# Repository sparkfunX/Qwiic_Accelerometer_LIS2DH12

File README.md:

Qwiic Accelerometer LIS2DH12
=======================================

This MEMS, three axis accelerometer by STMicroelectronics has been outfitted to communicate over Qwiic. The LIS2DH12 is an ultra-low-power highperformance three-axis linear accelerometer belonging to the “femto” family with digital I2C/SPI serial interface standard output.

Repository Contents
-------------------

* **/Hardware** - Eagle design files (.brd, .sch)
* **/Documents** - Documentation
* **/LIS2DH12_test** - Test Script

License Information
-------------------

This product is _**open source**_! 

Please review the LICENSE.md file for license information. 

If you have any questions or concerns on licensing, please contact technical support on our [SparkFun forums](https://forum.sparkfun.com/viewforum.php?f=152).

Distributed as-is; no warranty is given.

- Your friends at SparkFun.

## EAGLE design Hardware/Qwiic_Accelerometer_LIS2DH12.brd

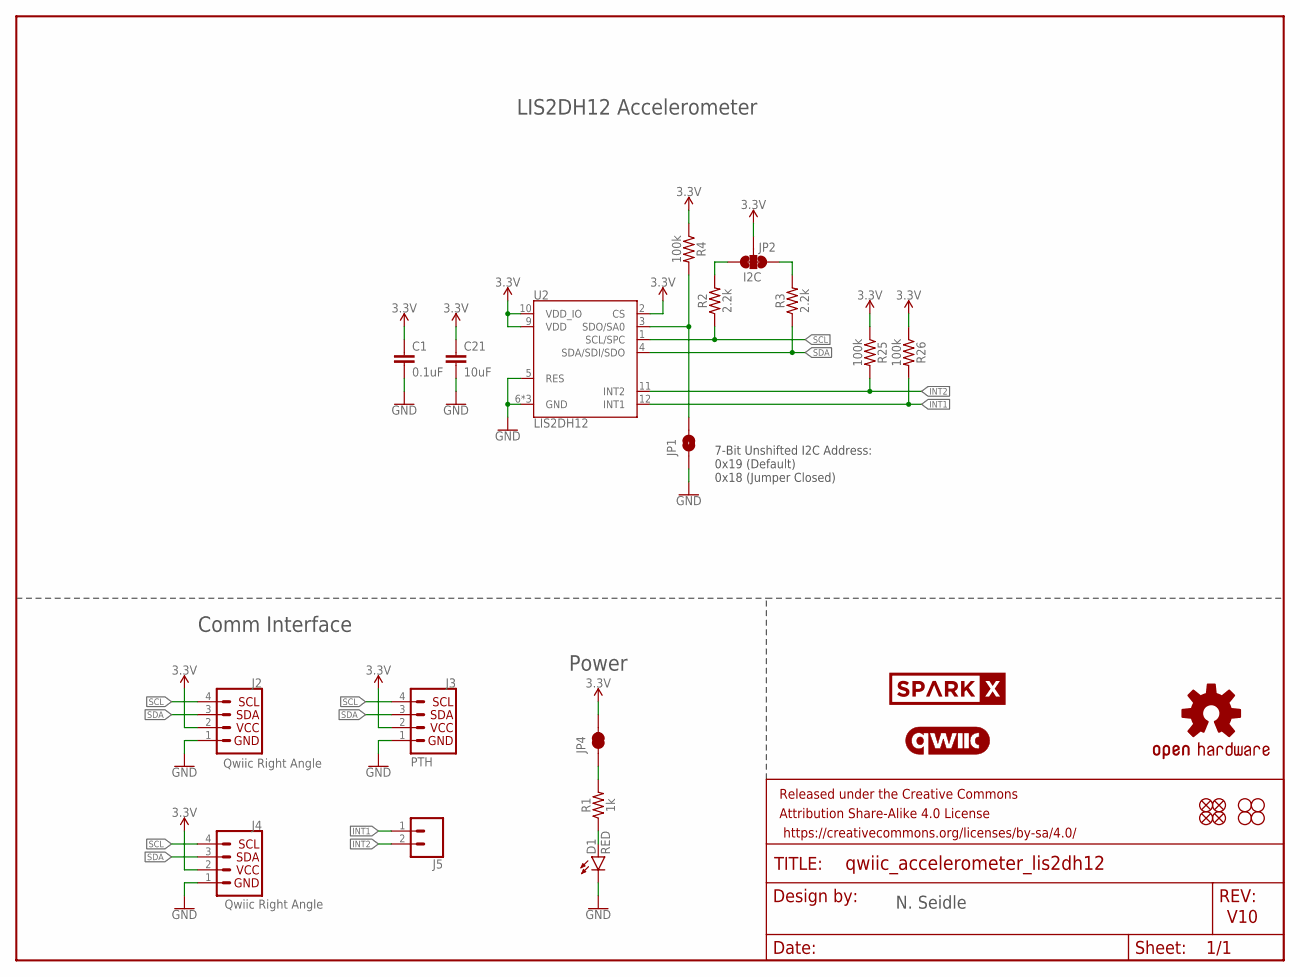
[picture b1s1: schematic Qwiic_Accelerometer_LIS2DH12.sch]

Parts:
C1: 0.1uF; 0603
C21: 10uF; 0603
D1: RED; LED-0603
FD1, FD2, FD3, FD4: FIDUCIALUFIDUCIAL; FIDUCIAL-MICRO
FRAME1: FRAME-LETTER; CREATIVE_COMMONS
H1, H2, H3, H4: STAND-OFF
J2, J4: Qwiic Right Angle; JST04_1MM_RA
J3: PTH; 1X04_NO_SILK
J5: CONN_021X02_NO_SILK; 1X02_NO_SILK
JP1: JUMPER-SMT_2_NO_SILK; SMT-JUMPER_2_NO_SILK
JP2: I2C; SMT-JUMPER_3_2-NC_TRACE_SILK
JP4: JUMPER-SMT_2_NC_TRACE_SILK; SMT-JUMPER_2_NC_TRACE_SILK
LOGO1: OSHW-LOGOMINI; OSHW-LOGO-MINI
LOGO4: QWIIC_LOGO_CONNECTOR; QWIIC_5.5MM
R1: 1k; 0603
R2, R3: 2.2k; 0603
R4, R25, R26: 100k; 0603
U2: LIS2DH12; LGA-12-LISDH12
U$30: SPARKX-LOGO4; SPARKX-MEDIUM

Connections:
3.3V: C1.1, C21.1, J2.2, J3.2, J4.2, JP2.2, JP4.2, R4.1, R25.1, R26.1, U2.2 (CS), U2.9 (VDD), U2.10 (VDD_IO)
GND: C1.2, C21.2, D1.C, J2.1, J3.1, J4.1, JP1.1, U2.5 (RES), U2.6 (GND), U2.7 (GND), U2.8 (GND)
INT1: J5.1, R26.2, U2.12 (INT1)
INT2: J5.2, R25.2, U2.11 (INT2)
unnamed: JP4.1, R1.2
unnamed: JP2.1, R3.2
unnamed: JP2.3, R2.2
unnamed: JP1.2, R4.2, U2.3 (SDO/SA0)
unnamed: D1.A, R1.1
SCL: J2.4, J3.4, J4.4, R2.1, U2.1 (SCL/SPC)
SDA: J2.3, J3.3, J4.3, R3.1, U2.4 (SDA/SDI/SDO)

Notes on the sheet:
V10
N. Seidle
LIS2DH12 Accelerometer
Comm Interface
Power
7-Bit Unshifted I2C Address: 0x19 (Default) 0x18 (Jumper Closed)

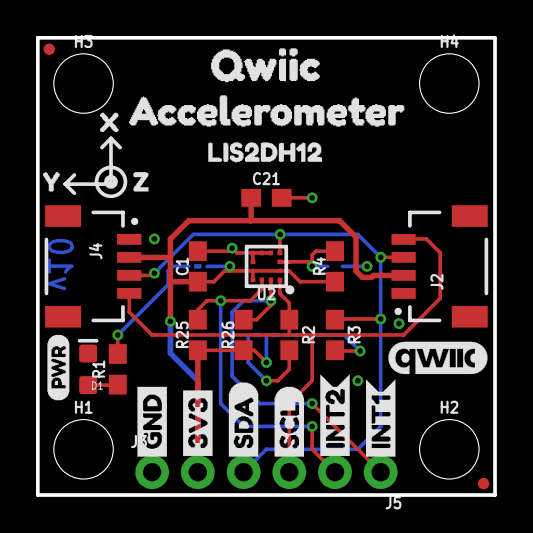
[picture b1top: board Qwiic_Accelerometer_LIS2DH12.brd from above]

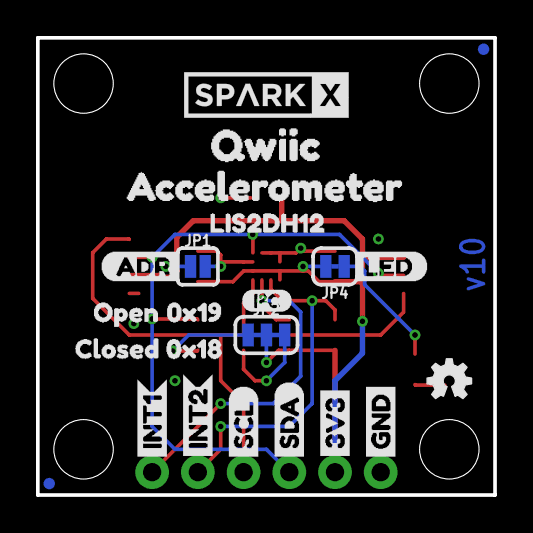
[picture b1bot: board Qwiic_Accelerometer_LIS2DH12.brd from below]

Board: 2 copper layers, 25.4 x 25.4 mm, 58 parts (23 on the bottom side), 11 nets.

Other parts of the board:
U$1, U$4: SDA-[)
U$2: X0
U$3, U$5: SCL-[)
U$6, U$7: 3V3-04
U$8, U$9: GND-04
U$10, U$27: ACCELEROMETER2
U$11, U$12: INT13
U$13, U$15: INT24
U$14, U$22: QWIIC2
U$16: 0X183
U$17, U$28: LIS2DH120
U$18: PWR-()-03
U$19: I_SUPER2_C-()-03
U$20: Y1
U$21: Z2
U$23: 0X192
U$24: ADR1
U$25: CLOSED4
U$26: OPEN5
U$29: LED7

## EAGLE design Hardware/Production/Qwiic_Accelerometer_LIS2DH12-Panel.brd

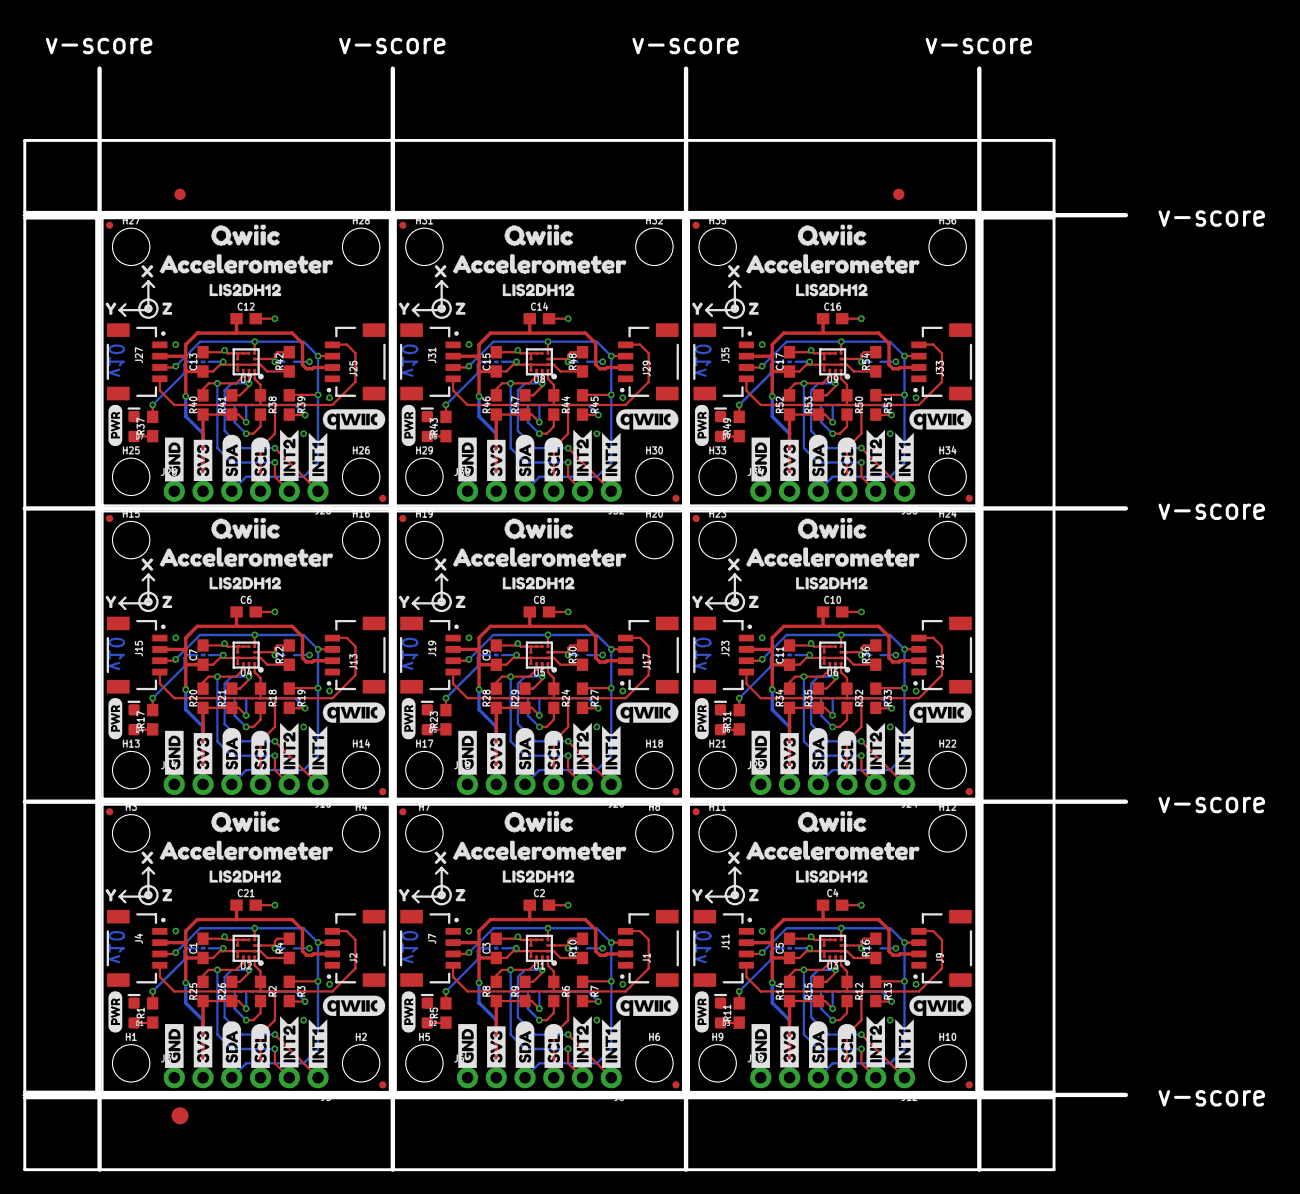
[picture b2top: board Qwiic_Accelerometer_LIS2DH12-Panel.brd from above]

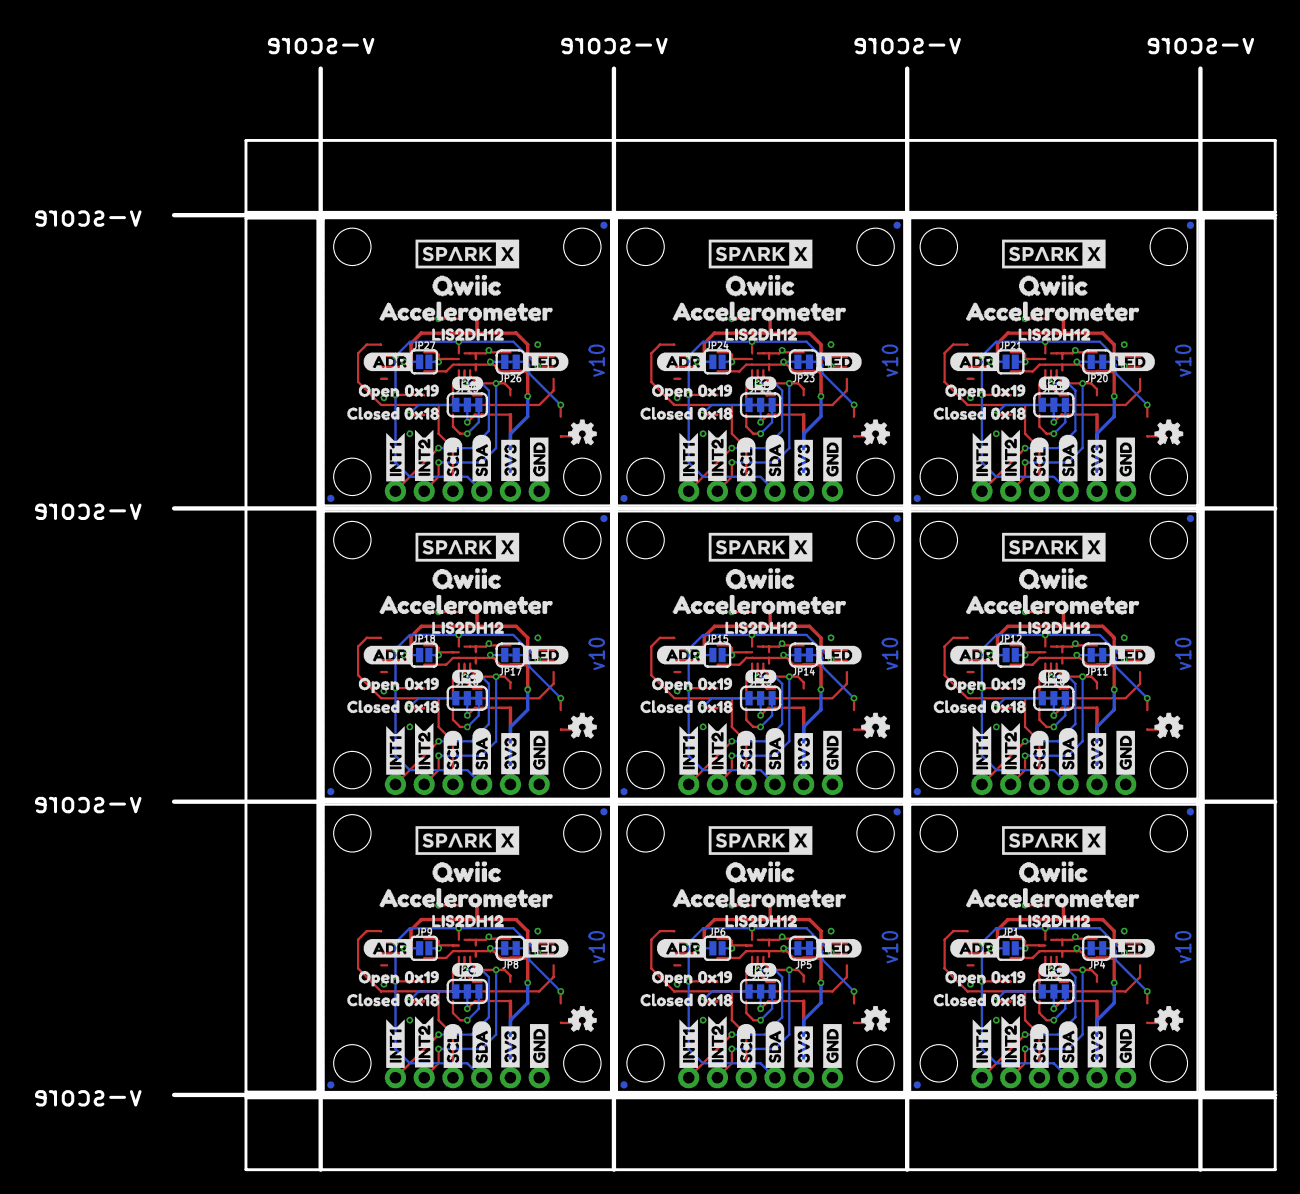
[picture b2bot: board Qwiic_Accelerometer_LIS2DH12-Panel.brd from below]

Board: 2 copper layers, 110.5 x 101.2 mm, 516 parts (207 on the bottom side), 99 nets.

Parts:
C1, C3, C5, C7, C9, C11, C13, C15, C17: 0.1uF; 0603
C2, C4, C6, C8, C10, C12, C14, C16, C21: 10uF; 0603
D1, D2, D3, D4, D5, D6, D7, D8, D9: RED; LED-0603
E$1, E$2: FIDUCIAL-1X2
E$3: FIDUCIAL-1.5X3
FD1, FD2, FD3, FD4, FD5, FD6, FD7, FD8, FD9, FD10, FD11, FD12, FD13, FD14, FD15, FD16, FD17, FD18, FD19, FD20, FD21, FD22, FD23, FD24, FD25, FD26, FD27, FD28, FD29, FD30, FD31, FD32, FD33, FD34, FD35, FD36: FIDUCIALUFIDUCIAL; FIDUCIAL-MICRO
H1, H2, H3, H4, H5, H6, H7, H8, H9, H10, H11, H12, H13, H14, H15, H16, H17, H18, H19, H20, H21, H22, H23, H24, H25, H26, H27, H28, H29, H30, H31, H32, H33, H34, H35, H36: STAND-OFF
J1, J2, J4, J7, J9, J11, J13, J15, J17, J19, J21, J23, J25, J27, J29, J31, J33, J35: Qwiic Right Angle; JST04_1MM_RA
J3, J6, J10, J14, J18, J22, J26, J30, J34: PTH; 1X04_NO_SILK
J5, J8, J12, J16, J20, J24, J28, J32, J36: 1X02_NO_SILK
JP1, JP6, JP9, JP12, JP15, JP18, JP21, JP24, JP27: SMT-JUMPER_2_NO_SILK
JP2, JP3, JP7, JP10, JP13, JP16, JP19, JP22, JP25: I2C; SMT-JUMPER_3_2-NC_TRACE_SILK
JP4, JP5, JP8, JP11, JP14, JP17, JP20, JP23, JP26: SMT-JUMPER_2_NC_TRACE_SILK
LOGO1, LOGO2, LOGO5, LOGO7, LOGO9, LOGO11, LOGO13, LOGO15, LOGO17: OSHW-LOGOMINI; OSHW-LOGO-MINI
LOGO3, LOGO4, LOGO6, LOGO8, LOGO10, LOGO12, LOGO14, LOGO16, LOGO18: QWIIC_LOGO_CONNECTOR; QWIIC_5.5MM
R1, R5, R11, R17, R23, R31, R37, R43, R49: 1k; 0603
R2, R3, R6, R7, R12, R13, R18, R19, R24, R27, R32, R33, R38, R39, R44, R45, R50, R51: 2.2k; 0603
R4, R8, R9, R10, R14, R15, R16, R20, R21, R22, R25, R26, R28, R29, R30, R34, R35, R36, R40, R41, R42, R46, R47, R48, R52, R53, R54: 100k; 0603
U1, U2, U3, U4, U5, U6, U7, U8, U9: LIS2DH12; LGA-12-LISDH12
U$1, U$4, U$31, U$33, U$61, U$63, U$91, U$93, U$121, U$123, U$151, U$153, U$181, U$183, U$211, U$213, U$241, U$243: SDA-[)
U$2, U$49, U$79, U$109, U$139, U$169, U$199, U$229, U$259: X0
U$3, U$5, U$32, U$34, U$62, U$64, U$92, U$94, U$122, U$124, U$152, U$154, U$182, U$184, U$212, U$214, U$242, U$244: SCL-[)
U$6, U$7, U$35, U$36, U$65, U$66, U$95, U$96, U$125, U$126, U$155, U$156, U$185, U$186, U$215, U$216, U$245, U$246: 3V3-04
U$8, U$9, U$37, U$38, U$67, U$68, U$97, U$98, U$127, U$128, U$157, U$158, U$187, U$188, U$217, U$218, U$247, U$248: GND-04
U$10, U$27, U$43, U$56, U$73, U$86, U$103, U$116, U$133, U$146, U$163, U$176, U$193, U$206, U$223, U$236, U$253, U$266: ACCELEROMETER2
U$11, U$12, U$44, U$45, U$74, U$75, U$104, U$105, U$134, U$135, U$164, U$165, U$194, U$195, U$224, U$225, U$254, U$255: INT13
U$13, U$15, U$46, U$47, U$76, U$77, U$106, U$107, U$136, U$137, U$166, U$167, U$196, U$197, U$226, U$227, U$256, U$257: INT24
U$14, U$22, U$40, U$42, U$70, U$72, U$100, U$102, U$130, U$132, U$160, U$162, U$190, U$192, U$220, U$222, U$250, U$252: QWIIC2
U$16, U$52, U$82, U$112, U$142, U$172, U$202, U$232, U$262: 0X183
U$17, U$28, U$48, U$57, U$78, U$87, U$108, U$117, U$138, U$147, U$168, U$177, U$198, U$207, U$228, U$237, U$258, U$267: LIS2DH120
U$18, U$39, U$69, U$99, U$129, U$159, U$189, U$219, U$249: PWR-()-03
U$19, U$41, U$71, U$101, U$131, U$161, U$191, U$221, U$251: I_SUPER2_C-()-03
U$20, U$50, U$80, U$110, U$140, U$170, U$200, U$230, U$260: Y1
U$21, U$51, U$81, U$111, U$141, U$171, U$201, U$231, U$261: Z2
U$23, U$53, U$83, U$113, U$143, U$173, U$203, U$233, U$263: 0X192
U$24, U$54, U$84, U$114, U$144, U$174, U$204, U$234, U$264: ADR1
U$25, U$55, U$85, U$115, U$145, U$175, U$205, U$235, U$265: CLOSED4
U$26, U$59, U$89, U$119, U$149, U$179, U$209, U$239, U$269: OPEN5
U$29, U$58, U$88, U$118, U$148, U$178, U$208, U$238, U$268: LED7
U$30, U$60, U$90, U$120, U$150, U$180, U$210, U$240, U$270: SPARKX-LOGO4; SPARKX-MEDIUM

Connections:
3.3V: C1.1, C21.1, J2.2, J3.2, J4.2, JP2.2, JP4.2, R4.1, R25.1, R26.1, U2.2, U2.9, U2.10
3.3V1: C2.1, C3.1, J1.2, J6.2, J7.2, JP3.2, JP5.2, R8.1, R9.1, R10.1, U1.2, U1.9, U1.10
3.3V2: C4.1, C5.1, J9.2, J10.2, J11.2, JP7.2, JP8.2, R14.1, R15.1, R16.1, U3.2, U3.9, U3.10
3.3V3: C6.1, C7.1, J13.2, J14.2, J15.2, JP10.2, JP11.2, R20.1, R21.1, R22.1, U4.2, U4.9, U4.10
3.3V4: C8.1, C9.1, J17.2, J18.2, J19.2, JP13.2, JP14.2, R28.1, R29.1, R30.1, U5.2, U5.9, U5.10
3.3V5: C10.1, C11.1, J21.2, J22.2, J23.2, JP16.2, JP17.2, R34.1, R35.1, R36.1, U6.2, U6.9, U6.10
3.3V6: C12.1, C13.1, J25.2, J26.2, J27.2, JP19.2, JP20.2, R40.1, R41.1, R42.1, U7.2, U7.9, U7.10
3.3V7: C14.1, C15.1, J29.2, J30.2, J31.2, JP22.2, JP23.2, R46.1, R47.1, R48.1, U8.2, U8.9, U8.10
3.3V8: C16.1, C17.1, J33.2, J34.2, J35.2, JP25.2, JP26.2, R52.1, R53.1, R54.1, U9.2, U9.9, U9.10
GND: C1.2, C21.2, D1.C, J2.1, J3.1, J4.1, JP1.1, U2.5, U2.6, U2.7, U2.8
GND1: C2.2, C3.2, D2.C, J1.1, J6.1, J7.1, JP6.1, U1.5, U1.6, U1.7, U1.8
GND2: C4.2, C5.2, D3.C, J9.1, J10.1, J11.1, JP9.1, U3.5, U3.6, U3.7, U3.8
GND3: C6.2, C7.2, D4.C, J13.1, J14.1, J15.1, JP12.1, U4.5, U4.6, U4.7, U4.8
GND4: C8.2, C9.2, D5.C, J17.1, J18.1, J19.1, JP15.1, U5.5, U5.6, U5.7, U5.8
GND5: C10.2, C11.2, D6.C, J21.1, J22.1, J23.1, JP18.1, U6.5, U6.6, U6.7, U6.8
GND6: C12.2, C13.2, D7.C, J25.1, J26.1, J27.1, JP21.1, U7.5, U7.6, U7.7, U7.8
GND7: C14.2, C15.2, D8.C, J29.1, J30.1, J31.1, JP24.1, U8.5, U8.6, U8.7, U8.8
GND8: C16.2, C17.2, D9.C, J33.1, J34.1, J35.1, JP27.1, U9.5, U9.6, U9.7, U9.8
INT1: J5.1, R26.2, U2.12
INT2: J5.2, R25.2, U2.11
INT3: J8.1, R9.2, U1.12
INT4: J8.2, R8.2, U1.11
INT5: J12.1, R15.2, U3.12
INT6: J12.2, R14.2, U3.11
INT7: J16.1, R21.2, U4.12
INT8: J16.2, R20.2, U4.11
INT9: J20.1, R29.2, U5.12
INT10: J20.2, R28.2, U5.11
INT11: J24.1, R35.2, U6.12
INT12: J24.2, R34.2, U6.11
INT13: J28.1, R41.2, U7.12
INT14: J28.2, R40.2, U7.11
INT15: J32.1, R47.2, U8.12
INT16: J32.2, R46.2, U8.11
INT17: J36.1, R53.2, U9.12
INT18: J36.2, R52.2, U9.11
unnamed: JP4.1, R1.2
unnamed: JP2.1, R3.2
unnamed: JP2.3, R2.2
unnamed: JP1.2, R4.2, U2.3
unnamed: D2.A, R5.1
unnamed: JP3.1, R7.2
unnamed: JP3.3, R6.2
unnamed: JP5.1, R5.2
unnamed: JP6.2, R10.2, U1.3
unnamed: D1.A, R1.1
unnamed: D3.A, R11.1
unnamed: JP7.1, R13.2
unnamed: JP7.3, R12.2
unnamed: JP8.1, R11.2
unnamed: JP9.2, R16.2, U3.3
unnamed: D4.A, R17.1
unnamed: JP10.1, R19.2
unnamed: JP10.3, R18.2
unnamed: JP11.1, R17.2
unnamed: JP12.2, R22.2, U4.3
unnamed: D5.A, R23.1
unnamed: JP13.1, R27.2
unnamed: JP13.3, R24.2
unnamed: JP14.1, R23.2
unnamed: JP15.2, R30.2, U5.3
unnamed: D6.A, R31.1
unnamed: JP16.1, R33.2
unnamed: JP16.3, R32.2
unnamed: JP17.1, R31.2
unnamed: JP18.2, R36.2, U6.3
unnamed: D7.A, R37.1
unnamed: JP19.1, R39.2
unnamed: JP19.3, R38.2
unnamed: JP20.1, R37.2
unnamed: JP21.2, R42.2, U7.3
unnamed: D8.A, R43.1
unnamed: JP22.1, R45.2
unnamed: JP22.3, R44.2
unnamed: JP23.1, R43.2
unnamed: JP24.2, R48.2, U8.3
unnamed: D9.A, R49.1
unnamed: JP25.1, R51.2
unnamed: JP25.3, R50.2
unnamed: JP26.1, R49.2
unnamed: JP27.2, R54.2, U9.3
SCL: J2.4, J3.4, J4.4, R2.1, U2.1
SCL1: J1.4, J6.4, J7.4, R6.1, U1.1
SCL2: J9.4, J10.4, J11.4, R12.1, U3.1
SCL3: J13.4, J14.4, J15.4, R18.1, U4.1
SCL4: J17.4, J18.4, J19.4, R24.1, U5.1
SCL5: J21.4, J22.4, J23.4, R32.1, U6.1
SCL6: J25.4, J26.4, J27.4, R38.1, U7.1
SCL7: J29.4, J30.4, J31.4, R44.1, U8.1
SCL8: J33.4, J34.4, J35.4, R50.1, U9.1
SDA: J2.3, J3.3, J4.3, R3.1, U2.4
SDA1: J1.3, J6.3, J7.3, R7.1, U1.4
SDA2: J9.3, J10.3, J11.3, R13.1, U3.4
SDA3: J13.3, J14.3, J15.3, R19.1, U4.4
SDA4: J17.3, J18.3, J19.3, R27.1, U5.4
SDA5: J21.3, J22.3, J23.3, R33.1, U6.4
SDA6: J25.3, J26.3, J27.3, R39.1, U7.4
SDA7: J29.3, J30.3, J31.3, R45.1, U8.4
SDA8: J33.3, J34.3, J35.3, R51.1, U9.4

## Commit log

2020-02-07 Added LIS2DH12 test script
2020-11-23 Created README and added license

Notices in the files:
parts and their libraries:
SparkFun-Resistors: Licensing: Creative Commons ShareAlike 4.0 International - https://creativecommons.org/licenses/by-sa/4.0
SparkFun-Aesthetics: Released under the Creative Commons Attribution Share-Alike 4.0 License
SparkFun-Aesthetics: https://creativecommons.org/licenses/by-sa/4.0
